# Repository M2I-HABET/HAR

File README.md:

# High Altitude Reporter (HAR)

HAR is named after the Norse god HÁR, the Norse god of knowledge whose name means "high." It seemed fitting then that we name our main onboard computer HAR.  HAR is used to gather data, store data, transmit data, and perform other housekeeping needs to keep the spacecraft functional through all stages of flight.

# Electrical Specification

HAR is the primary avionics system for all HABET missions. It provides a processing system, sensors, and communication functions to support all spacecraft missions.

## Electrical Overview

For all HABET missions, a few key things are needed to carry out a successful mission. To be successful, we need to have a system that allows us to track the spacecraft, communicate with the spacecraft, process sensor data, and manage power.

Generally speaking, Power and some sort of data management is usually the bare minimum needed for most payloads. However, many payloads either benefit or require the additional items listed. Therefore, Athena was designed with all of the items listed. As of the date of this document, the following features are currently provided.

| Feature | Specification |
| --- | --- |
| Power |  |
| LoRa Data link | 115,200 bps |
| Data Storage | Up to 2GB per payload |
| Data downlink | 1 packet every 4 seconds or higher. 1 packet must be under 256 bytes |
| Data uplink | 1 packet every 10 seconds or higher, 1 packet must be under 256 bytes |
| GPS Data | NMEA of the GPGGA string is available at 9600 bps |
| Video monitoring | Video stored onboard at 720p |

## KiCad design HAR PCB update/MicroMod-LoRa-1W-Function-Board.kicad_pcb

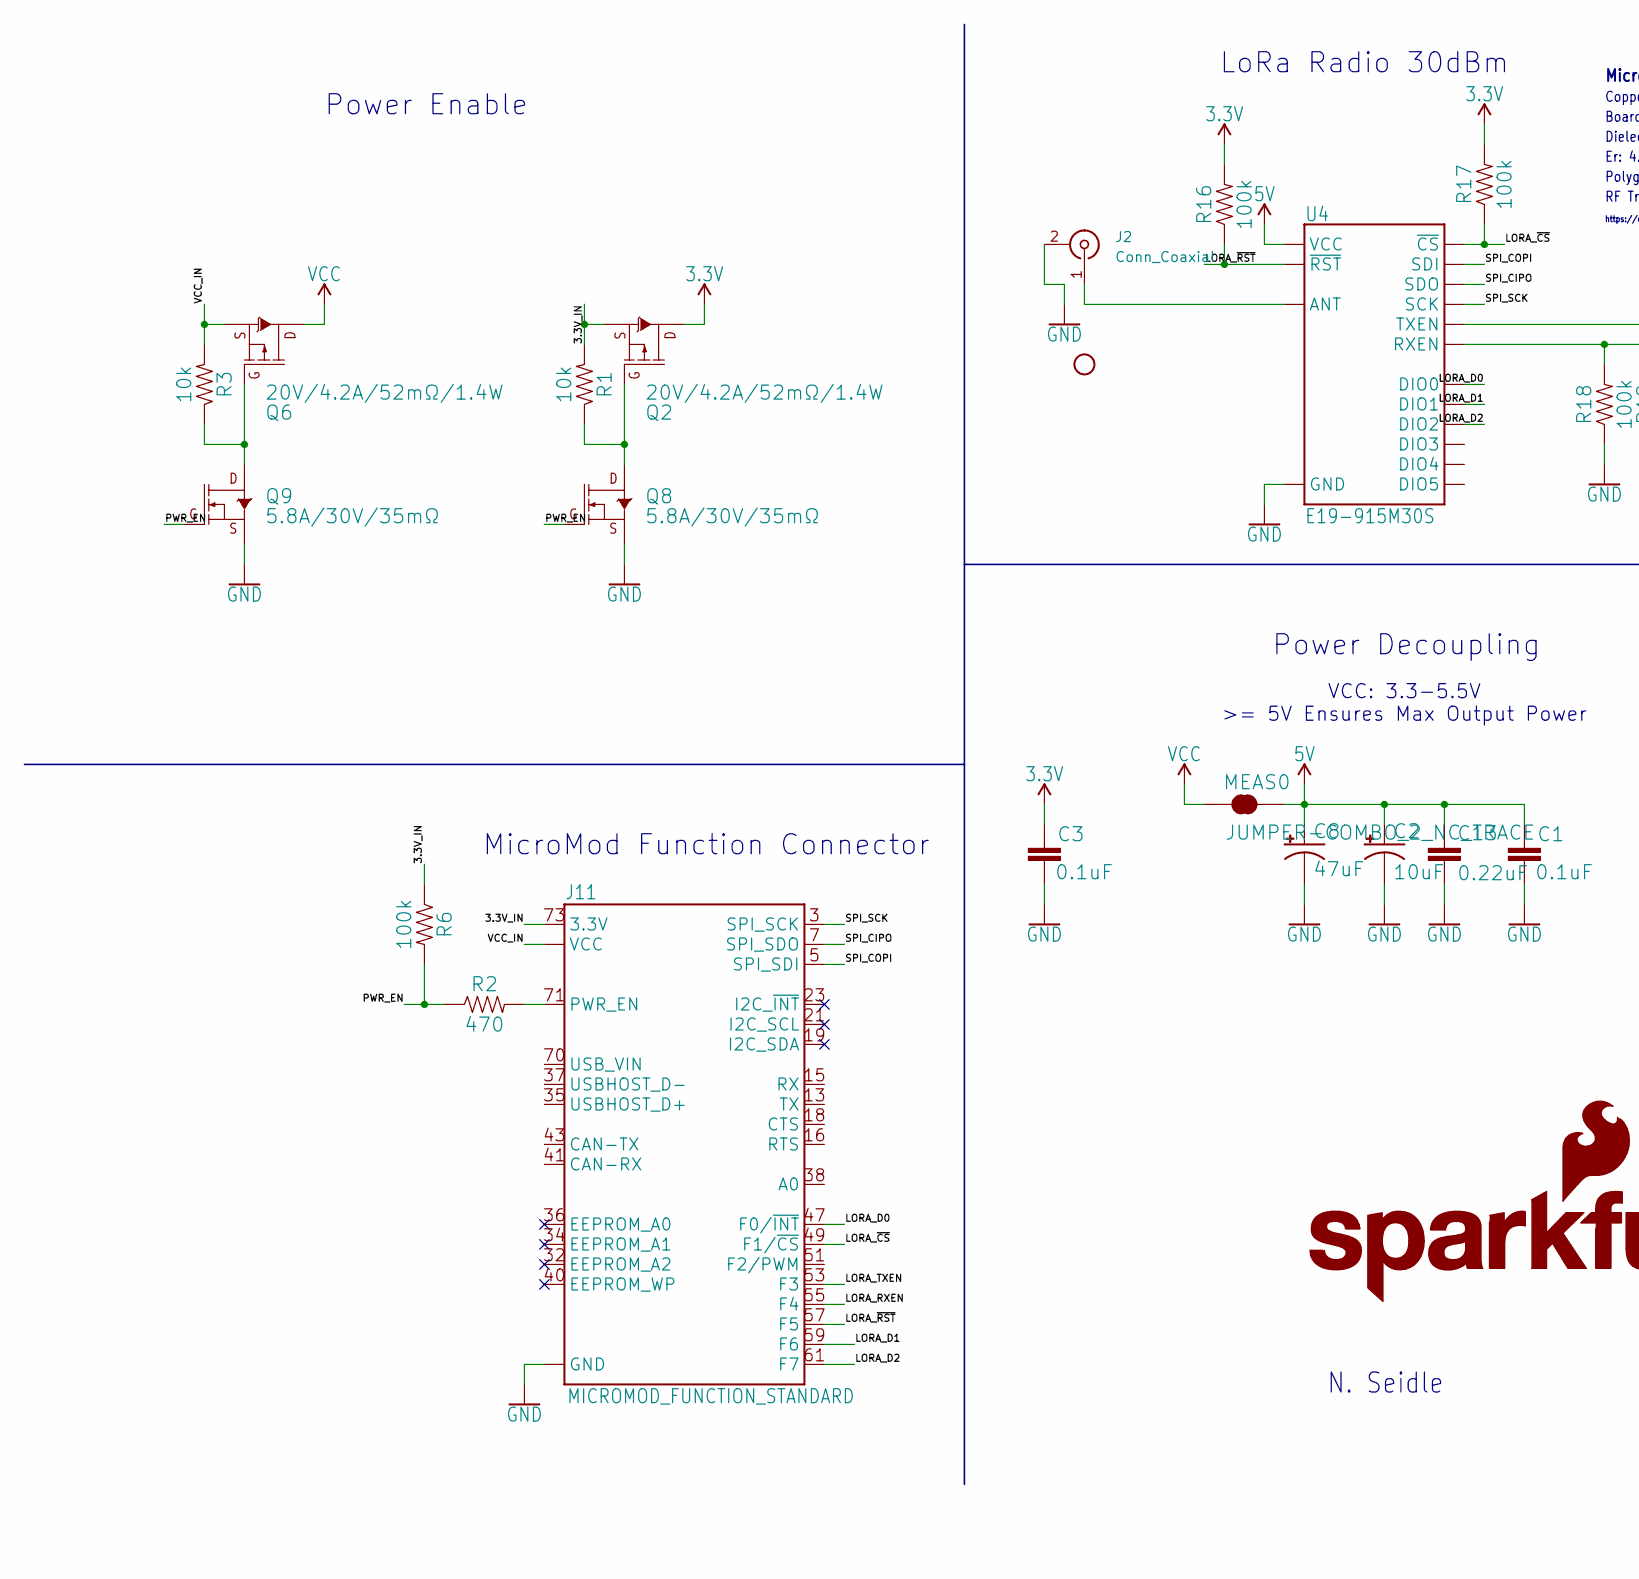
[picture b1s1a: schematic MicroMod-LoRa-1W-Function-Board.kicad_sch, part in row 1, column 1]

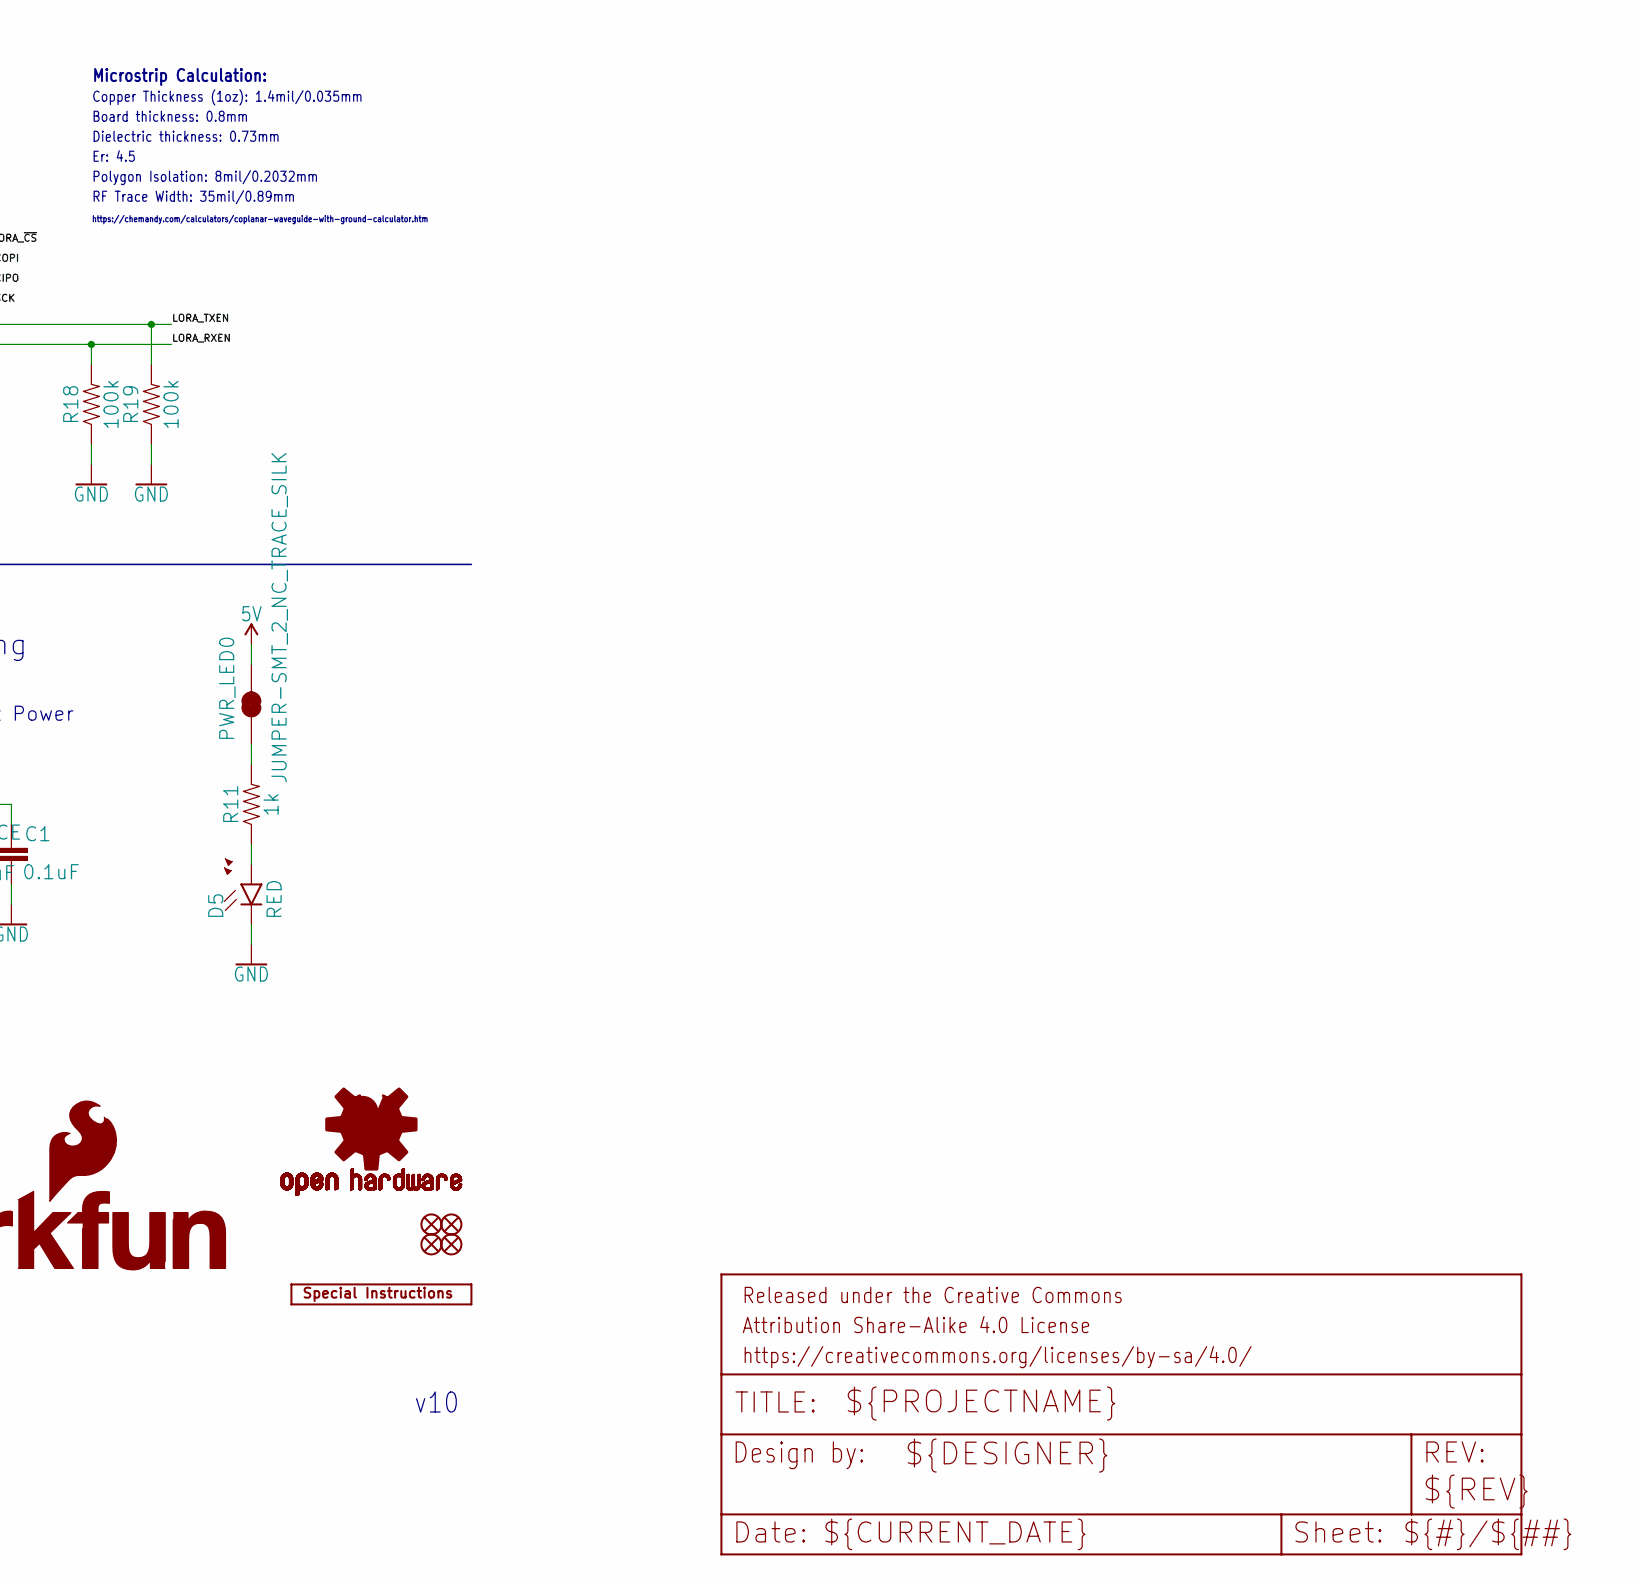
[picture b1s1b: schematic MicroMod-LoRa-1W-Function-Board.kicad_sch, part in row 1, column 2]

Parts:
C1, C3: 0.1uF; 0603
C2: 10uF; EIA3216
C8: 47uF; EIA3528
C13: 0.22uF; 0603
D5: RED; LED-0603
FD1, FD2, FD3, FD4: FIDUCIALUFIDUCIAL; FIDUCIAL-MICRO
FRAME2: FRAME-LETTER; CREATIVE_COMMONS
H1: STAND-OFF
J2: Conn_Coaxial; U.FL_Hirose_U.FL-R-SMT-1_Vertical
J11: MICROMOD_FUNCTION_STANDARD; M.2-CARD-E-22_FUNCTION_STANDARD
LOGO1: SFE_LOGO_NAME_FLAME.1_INCH; SFE_LOGO_NAME_FLAME_.1
LOGO2: SPECIAL_INSTRUCTIONS-ORDERING; ORDERING_INSTRUCTIONS
LOGO3: OSHW-LOGOMINI; OSHW-LOGO-MINI
MEAS0: JUMPER-COMBO_2_NC_TRACE; COMBO-JUMPER_2_NC_TRACE
PWR_LED0: JUMPER-SMT_2_NC_TRACE_SILK; SMT-JUMPER_2_NC_TRACE_SILK
Q2, Q6: 20V/4.2A/52mΩ/1.4W; SOT23-3
Q8, Q9: 5.8A/30V/35mΩ; SOT23-3
R1, R3: 10k; 0603
R2: 470; 0603
R6, R16, R17, R18, R19: 100k; 0603
R11: 1k; 0603
U4: E19-915M30S; E19-915MS1W

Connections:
3.3V: C3.1, Q2.3 (D), R16.2, R17.2
5V: C1.1, C2.+, C8.A (+), C13.1, MEAS0.2, MEAS0.4 (2), PWR_LED0.2, U4.11 (VCC)
/3.3V_IN: J11.73 (3.3V), Q2.2 (S), R1.2, R6.1
/LORA_D0: J11.47 (F0/~INT), U4.7 (DIO0)
/LORA_D1: J11.59 (F6), U4.6 (DIO1)
/LORA_D2: J11.61 (F7), U4.5 (DIO2)
/LORA_RXEN: J11.55 (F4), R18.2, U4.17 (RXEN)
/LORA_TXEN: J11.53 (F3), R19.2, U4.16 (TXEN)
/LORA_~CS: J11.49 (F1/~CS), R17.1, U4.15 (~CS)
/LORA_~RST: J11.57 (F5), R16.1, U4.8 (~RST)
/PWR_EN: Q8.1 (G), Q9.1 (G), R2.1, R6.2
/SPI_CIPO: J11.7 (SPI_SDO), U4.13 (SDO)
/SPI_COPI: J11.5 (SPI_SDI), U4.14 (SDI)
/SPI_SCK: J11.3 (SPI_SCK), U4.12 (SCK)
/VCC_IN: J11.72 (VCC), J11.74 (VCC), Q6.2 (S), R3.2
GND: C1.2, C2.-, C3.2, C8.C (-), C13.2, D5.C, J2.2 (Ext), J11.1 (GND), J11.33 (GND), J11.39 (GND), J11.45 (GND), J11.75 (GND), J11.GND1 (GND), J11.GND2 (GND), J11.GND3 (GND), J11.GND4 (GND), J11.GND5 (GND), J11.GND6 (GND), Q8.2 (S), Q9.2 (S), R18.1, R19.1, U4.1 (GND), U4.9 (GND), U4.10 (GND), U4.18 (GND), U4.20 (GND), U4.21 (GND), U4.22 (GND)
unnamed: D5.A, R11.1
unnamed: J2.1 (In), U4.19 (ANT)
unnamed: J11.71 (PWR_EN), R2.2
unnamed: PWR_LED0.1, R11.2
unnamed: Q2.1 (G), Q8.3 (D), R1.1
unnamed: Q6.1 (G), Q9.3 (D), R3.1
VCC: MEAS0.1, MEAS0.3 (1), Q6.3 (D)

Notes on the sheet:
N. Seidle
MicroMod Function Connector
Dielectric thickness: 0.73mm
https://chemandy.com/calculators/coplanar-waveguide-with-ground-calculator.htm
RF Trace Width: 35mil/0.89mm
LoRa Radio 30dBm
Board thickness: 0.8mm
Polygon Isolation: 8mil/0.2032mm
Power Decoupling
Copper Thickness (1oz): 1.4mil/0.035mm
Power Enable
v10
Microstrip Calculation:
Er: 4.5
VCC: 3.3-5.5V >= 5V Ensures Max Output Power

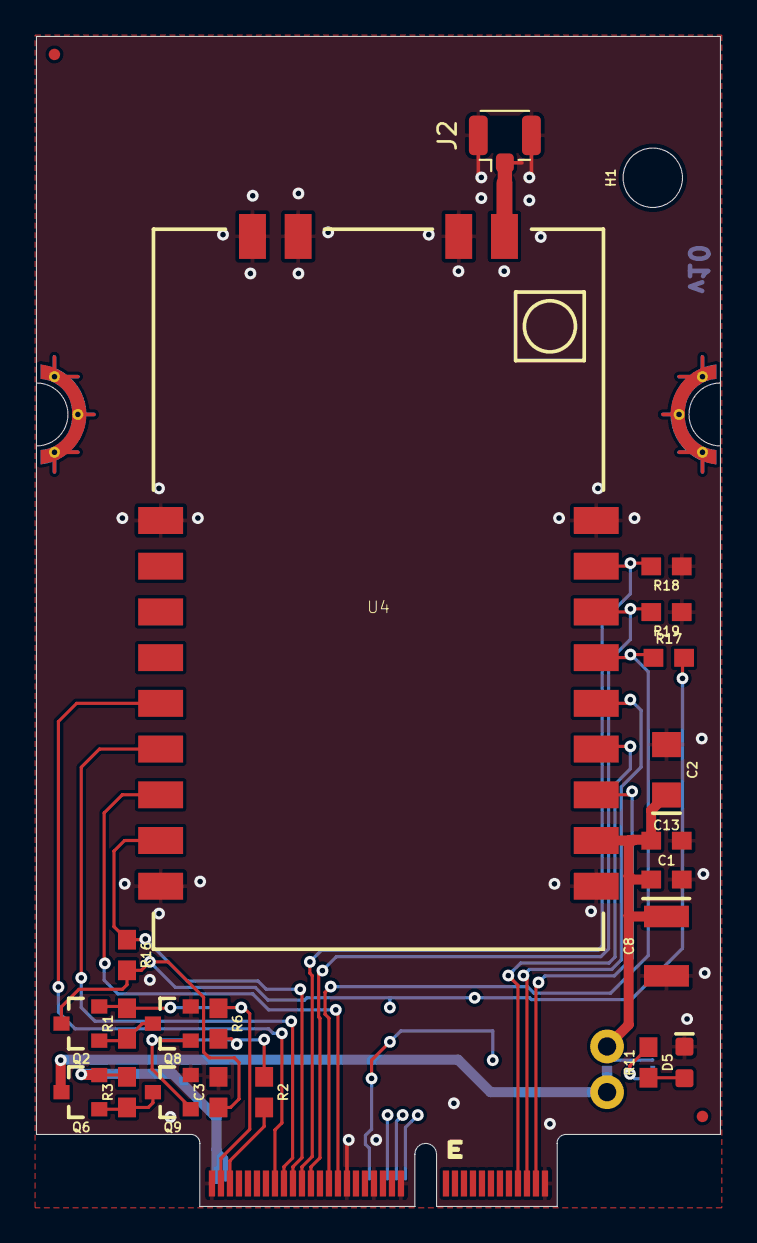
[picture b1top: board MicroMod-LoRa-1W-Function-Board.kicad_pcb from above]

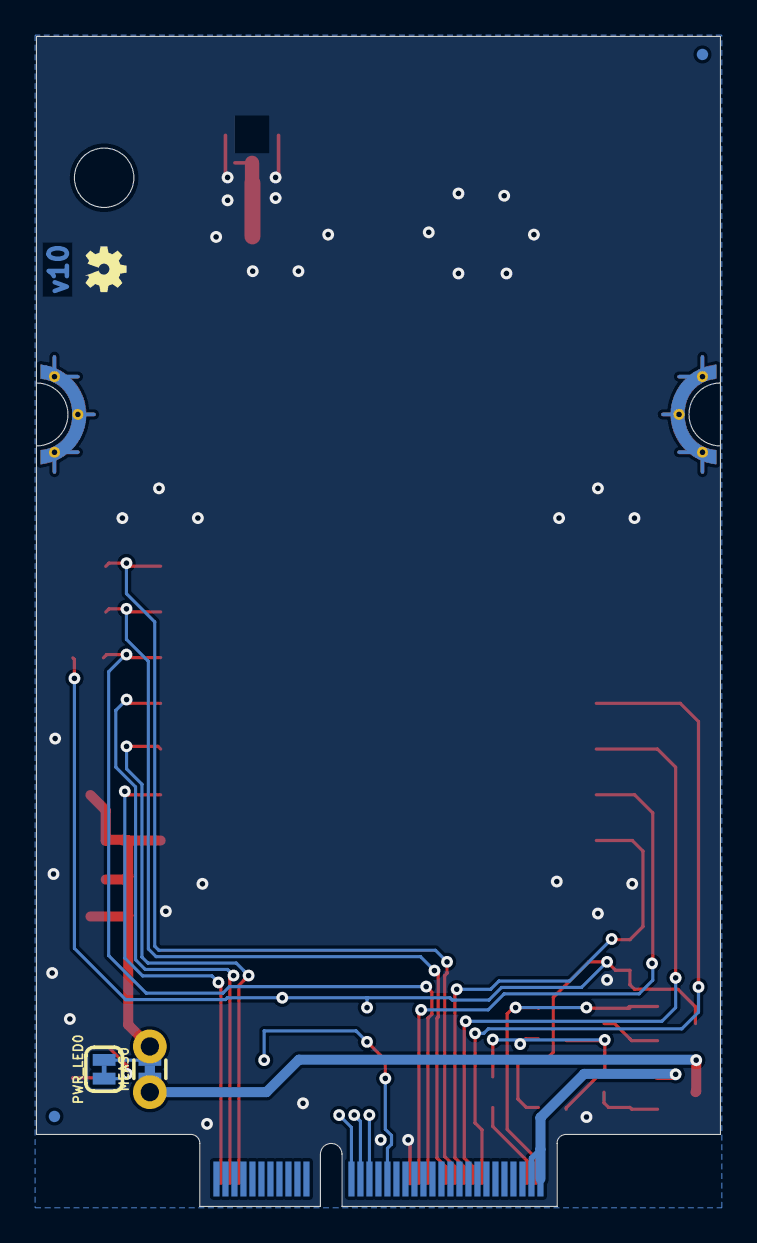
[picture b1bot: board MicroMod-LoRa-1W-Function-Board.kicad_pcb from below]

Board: 2 copper layers, 38.0 x 65.0 mm, 32 parts (5 on the bottom side), 23 nets.

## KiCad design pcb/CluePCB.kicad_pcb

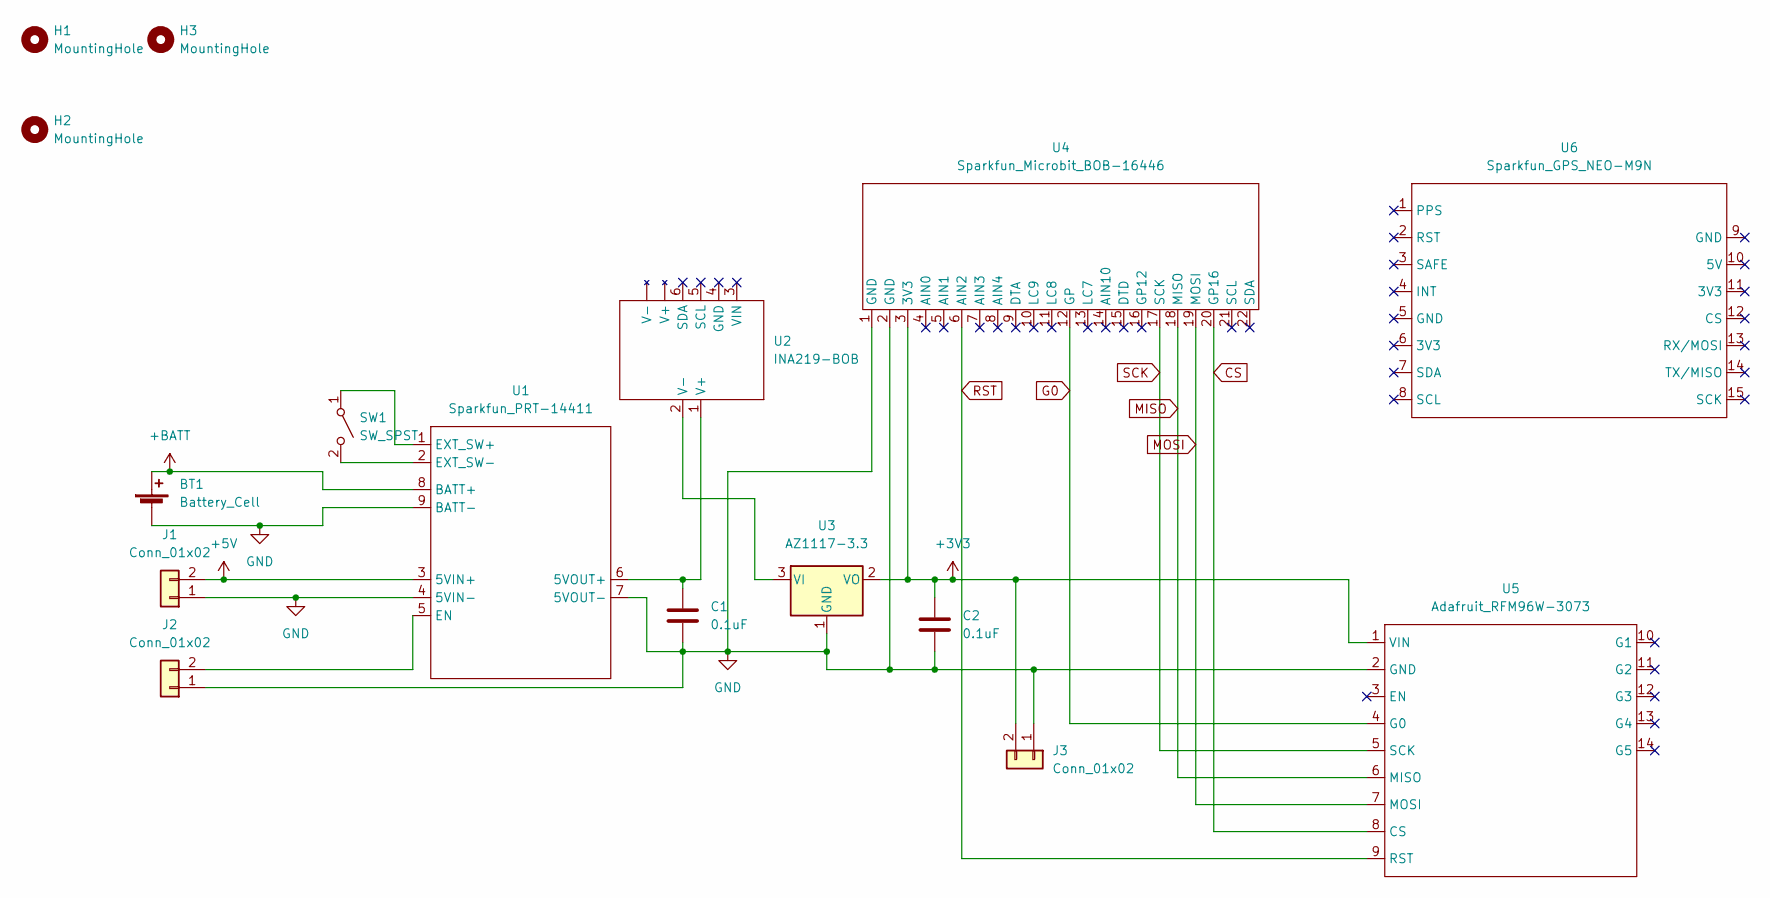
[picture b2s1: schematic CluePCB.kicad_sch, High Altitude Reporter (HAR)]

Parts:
BT1: Battery_Cell; BatteryHolder_Keystone_1042_1x18650
C1, C2: 0.1uF; C_Rect_L7.0mm_W4.5mm_P5.00mm
H1, H2, H3: MountingHole; MountingHole_3mm
J1, J2, J3: Conn_01x02; PinHeader_1x02_P2.54mm_Vertical
SW1: SW_SPST; PinHeader_1x02_P2.54mm_Vertical
U1: Sparkfun_PRT-14411; Sparkfun Boost BOB
U2: INA219-BOB; INA219
U3: AZ1117-3.3; TO-252-2
U4: Sparkfun_Microbit_BOB-16446; Sparkfun Microbit BOB
U5: Adafruit_RFM96W-3073; Adafruit LoRa BOB
U6: Sparkfun_GPS_NEO-M9N; Sparkfun GPS NEO M9N

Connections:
+3V3: C2.1, J3.2, U3.2 (VO), U4.3 (3V3), U5.1 (VIN)
+5V: J1.2, U1.3 (5VIN+)
+BATT: BT1.1 (+), U1.8 (BATT+)
CS: U4.20 (GP16), U5.8 (CS)
G0: U4.12 (GP), U5.4 (G0)
GND: BT1.2 (-), C1.2, C2.2, J1.1, J2.1, J3.1, U1.4 (5VIN-), U1.7 (5VOUT-), U1.9 (BATT-), U3.1 (GND), U4.1 (GND), U4.2 (GND), U5.2 (GND)
MISO: U4.18 (MISO), U5.6 (MISO)
MOSI: U4.19 (MOSI), U5.7 (MOSI)
unnamed: C1.1, U1.6 (5VOUT+), U2.1 (V+)
unnamed: J2.2, U1.5 (EN)
unnamed: SW1.1 (A), U1.1 (EXT_SW+)
unnamed: SW1.2 (B), U1.2 (EXT_SW-)
unnamed: U2.2 (V-), U3.3 (VI)
RST: U4.6 (AIN2), U5.9 (RST)
SCK: U4.17 (SCK), U5.5 (SCK)

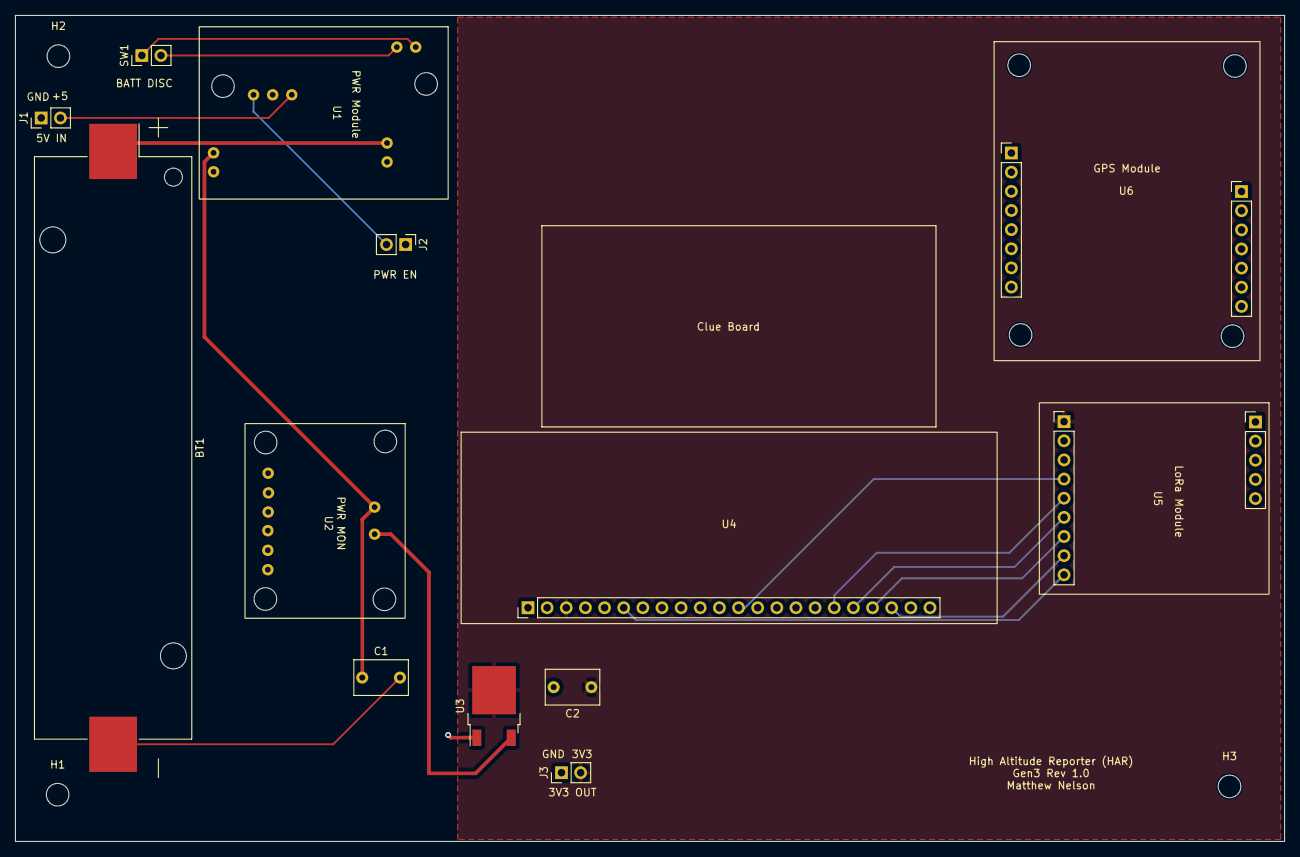
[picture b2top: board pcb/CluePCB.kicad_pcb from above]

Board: 2 copper layers, 168.4 x 109.6 mm, 16 parts (0 on the bottom side), 15 nets.

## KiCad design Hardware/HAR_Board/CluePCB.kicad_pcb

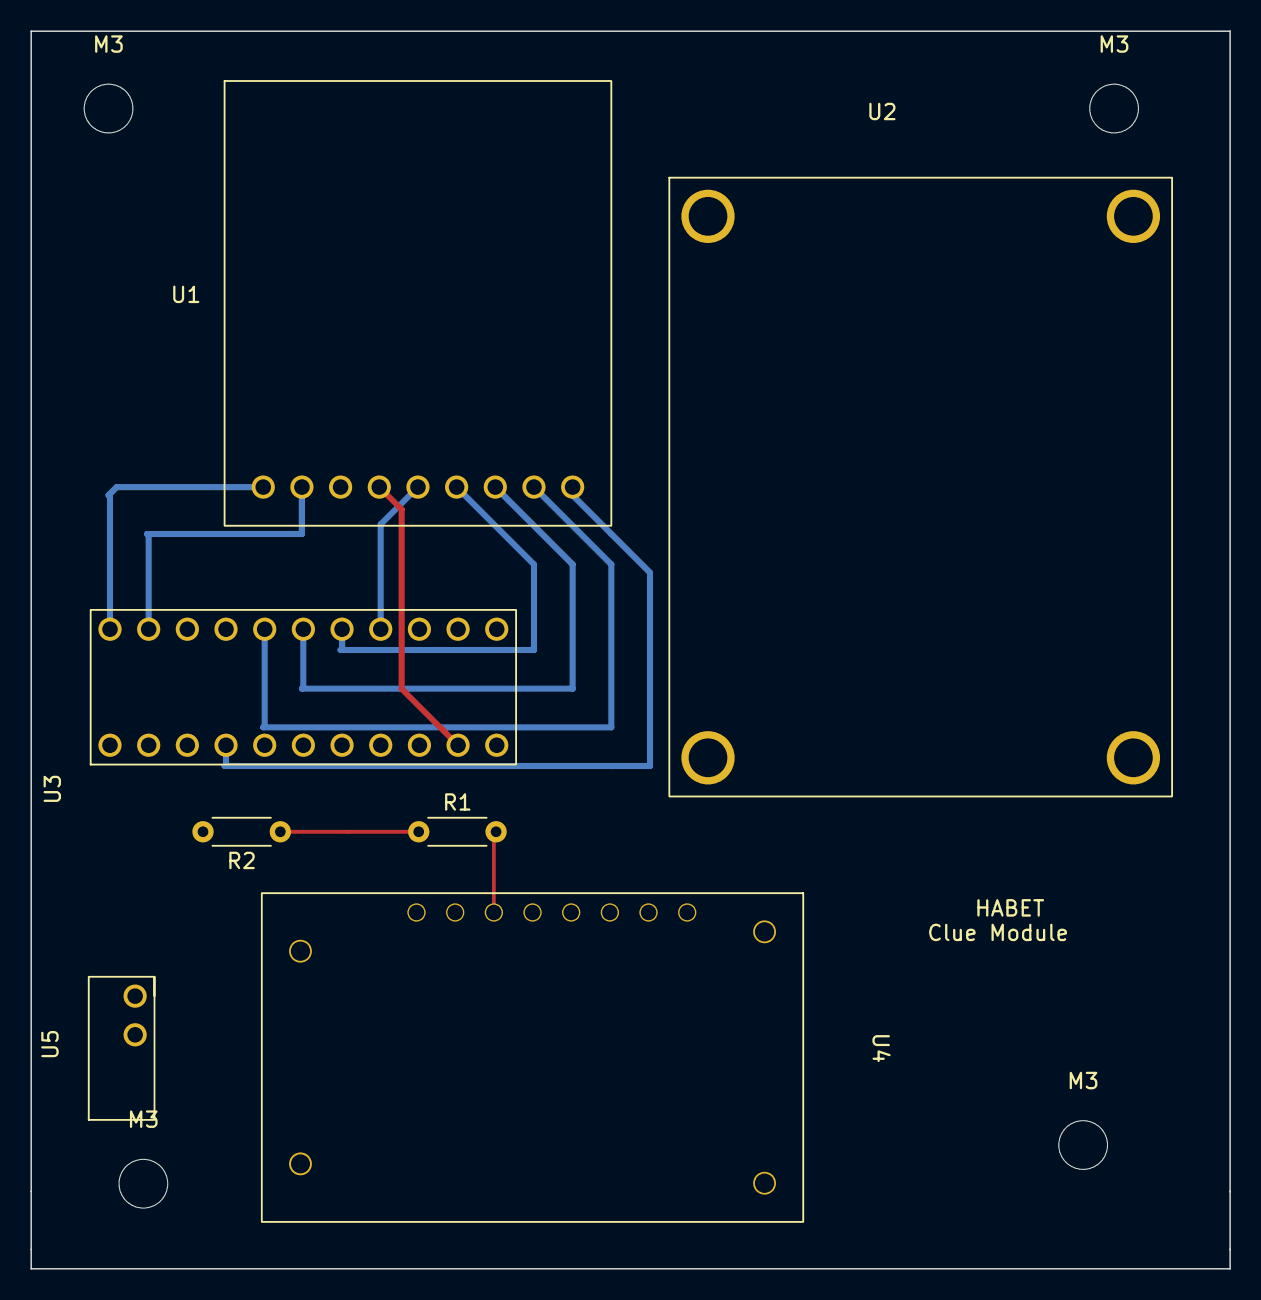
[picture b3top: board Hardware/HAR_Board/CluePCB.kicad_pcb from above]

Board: 2 copper layers, 78.7 x 81.3 mm, 11 parts (0 on the bottom side), 10 nets.

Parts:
M3, M3#2, M3#3, M3#4: MountingHole; MountingHole_3.2mm_M3
R1: 2.2k; R_Axial_DIN0204_L3.6mm_D1.6mm_P5.08mm_Horizontal
R2: 3.3k; R_Axial_DIN0204_L3.6mm_D1.6mm_P5.08mm_Horizontal
U1: LoRa
U2: GPS
U3: Dragontail
U4: PowerBoost500; Powerboost500
U5: Drag3V; Dragon3V

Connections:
unnamed: R1.1, R2.1
unnamed: R1.2, U4.3 (Bat)
unnamed: U1.1 (VIN), U3.20 (3V)
unnamed: U1.2 (GND), U3.19 (GND)
unnamed: U1.4 (G0), U3.8
unnamed: U1.5 (SCK), U3.13
unnamed: U1.6 (MISO), U3.14
unnamed: U1.7 (MOSI), U3.15
unnamed: U1.8 (CS), U3.16
unnamed: U1.9 (RST), U3.2

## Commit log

2021-07-22 initial code
    Initial code based on BERTOS
2021-07-23 Added Radiohead library and fixed issues so it compiles
2021-07-24 minor update
2021-07-25 Code re-work
    Re-worked the code to make it easier to add additional features. Moved GPS data into a struct and split much of the code in main into functions. Still needs work, but getting there.
2021-07-25 bug fixes
    bug fixes on some things not working on hardware
2021-07-26 Sending packets
    Packets being sent, needs code clean up but functional at this state.
2021-07-26 send and recieve
    demo of sending and receive packets.
2021-07-26 Added demo server
    Added a demo server that will work with this code.
2021-08-02 Server changed for safe handeling of bad strings
2021-08-02 initial udp to penthouse machine
2021-08-02 committing for merge
2021-08-09 Added logger to the server script
2021-08-09 Added logger to server script
2021-08-10 adding datalog for easy copying
2021-08-10 added gitignore
2021-08-13 Fix GPS, add Watchdog
    Did a fix to the GPS unit so it should work at high altitudes. Added a Watchdog feature in case the board locks up to reset after 10 seconds.
2021-08-13 Updates based on testing
2021-08-17 Removed dsstore
2021-10-01 Initial commit for hardware development
2021-10-13 Initial HW files
2021-10-13 committing for edits
2021-10-13 Attempting autoreconnect
2022-01-14 Small change
2022-03-28 Minor update
    Changed the filename and a few minor fixes based on last flight. Updated FW revision number
2022-06-30 Setup for new KiCad files
2022-07-01 Initial commit of KiCad files
2022-07-07 Add files via upload
    New voltage divider changes
2022-08-27 gitignore
2022-11-06 Added codeowners
2022-11-06 Reorganization
    Reorganization of files to prepare the repo for some future automation and to serve as a potential template for future projects.
2022-11-06 first draft on schematic
2022-11-06 First take on PCB
2022-11-07 Fixed some Footprints
2022-11-08 Updaates
2022-11-08 1st draft on board
    Board ready for first review. Added 3D parts into repo. LoRa does need some work for mounting holes
2022-11-08 Updated LoRa, started routing
2022-11-08 1st attempt at routing board
2022-11-09 Added LoRa datasheets
2022-11-10 Generated Gerber files
    Final update, generated gerber files
2022-12-05 Minor fix
2023-01-08 IMU part
2023-02-14 KiCad 7.0
2023-02-20 Fabrication run
2023-02-20 Not sure what changed
2023-02-20 Added power readings
2023-02-21 Added 3D model of board
2023-07-13 First version of HAR code for MicroMod board.
2023-07-18 Updated main.ino: changed initialization of GPS, cleaned up code, added comments for clarity
2023-07-25 Fixed errors. Added commented lines for sensor data and battery voltage.
2023-07-25 Changed last updated date.
2023-07-25 Updated BME 680 initialization. Sensor works now!
2023-07-28 Uploading early version of ground station code
2023-08-08 Very minor
2023-08-10 Changed radio output power and added decimals to sent data.
2023-10-05 Revised data string format. Changed GNSS dynamic model. Added dynamic pressure sensor functionality.
2023-11-04 Added SD card datalogging to HAR script. Needs testing! Removed lines for unnecessary sensors. Changed GPS initialization and changed how variables are called in loop.
2023-11-11 Changed library used for SD card storage. Still not working.
2023-11-21 Solved issues with SD card datalogging. Began implementation of receiver code on HAR.
2023-11-22 Implemented basic structure for sending commands from ground station to HAR. Needs further work.
2023-11-25 Updated functionality for sending/receiving commands. Not perfect, but it works. Need to implement checksum for CySat commands.
2024-02-21 Added watchdog timer to HAR main code.
2024-02-23 Unsuppressed RSSI signal strength data.
2024-03-01 Added additional GPS info to HAR data string.
2024-08-17 Latest version of HAR v5.
2024-09-16 Minor edit
2025-02-20 Re-organization
    Re-organization of the files for HAR v6. Moved over to PlatformIO for compiling of the source code.
2025-02-20 Actually adding code
2025-03-08 HAR Light FW
2025-03-08 final
2025-03-08 more testing needed
2025-03-08 Final for ground
2025-03-12 Update HAR_Ground_RFM95.ino for Sparkfun SX126/7/x
2025-03-13 Update HAR_Ground_RFM95.ino to include more libraries
2025-03-27 Update main.cpp
    A total refresh of the HAR firmware, with the ideal target being more succinct and easily readable.
2025-04-18 Create blank
2025-04-18 Create HARv5_receive
2025-04-18 Create HARv5_transmit
2025-04-18 Rename HARv5_receive to HARv5_receive.cpp
2025-04-18 Rename HARv5_transmit to HARv5_transmit.cpp
2025-04-18 Create platformio dependencies for both Tx & Rx
2025-06-17 Update HARv5_transmit.cpp for RadioHead library
    RadioLib removed, RadioHead has replaced it as a primary radio library.
2025-06-17 Update HARv5_receive.cpp for RadioHead Library
    Removed RadioLib and replaced with RadioHead.
2025-06-17 Update version and date last updated
2025-07-07 Created a version running the RadioHead library
    Swapped radio libraries from RadioLib to RadioHead to gain access to the power and low-noise amplifiers on the Ebyte E19 radio board.
2025-07-07 Create HARL_v1.0_Receiver
    Created a receiver software that can receive the primary HAR transmitted signal. This should be capable of receiving another RFM95 signal as well, so long as the radio settings are the same.
2025-07-07 Create placeholder
2025-07-07 Move HARv5.2_Receive.ino
    Swapped radio libraries from RadioLib to RadioHead to gain access to the power and low-noise amplifiers on the Ebyte E19 radio board.
2025-07-07 Move HARv5.2_Receive.ino
    Removed RadioLib and replaced with RadioHead.
2025-07-07 Delete HARv5/HARv5_Receive_RH.ino
    moved to HARv5.2
2025-07-07 Delete HARv5/HARv5_Transmit_RH.ino
    Moved to HARv5.2
2025-08-14 Rename HARv5_Receive_RH.ino to HARv5.2_Receive_RH.ino
2025-08-21 Rename HARv5.2_RH_Receive.ino to HARv5.2_RH_Receiver.ino
2026-04-02 adding the updated design of HAR
2026-04-02 the files for teh kicad project weren't imported properly
2026-04-02 adding the updated pcb files again
2026-04-03 Init to V6
2026-04-07 more updates
2026-05-21 slight update to reciever code.
2026-05-21 Minor change to reciever code.

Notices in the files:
HAR PCB update/MicroMod-LoRa-1W-Function-Board.kicad_sch:
Released under the Creative Commons
https://creativecommons.org/licenses/by-sa/4.0
parts and their libraries:
Released under the Creative Commons Attribution Share-Alike 4.0 License
